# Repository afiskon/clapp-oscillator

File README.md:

# clapp-oscillator
Clapp oscillator schematic, PCB and simulations

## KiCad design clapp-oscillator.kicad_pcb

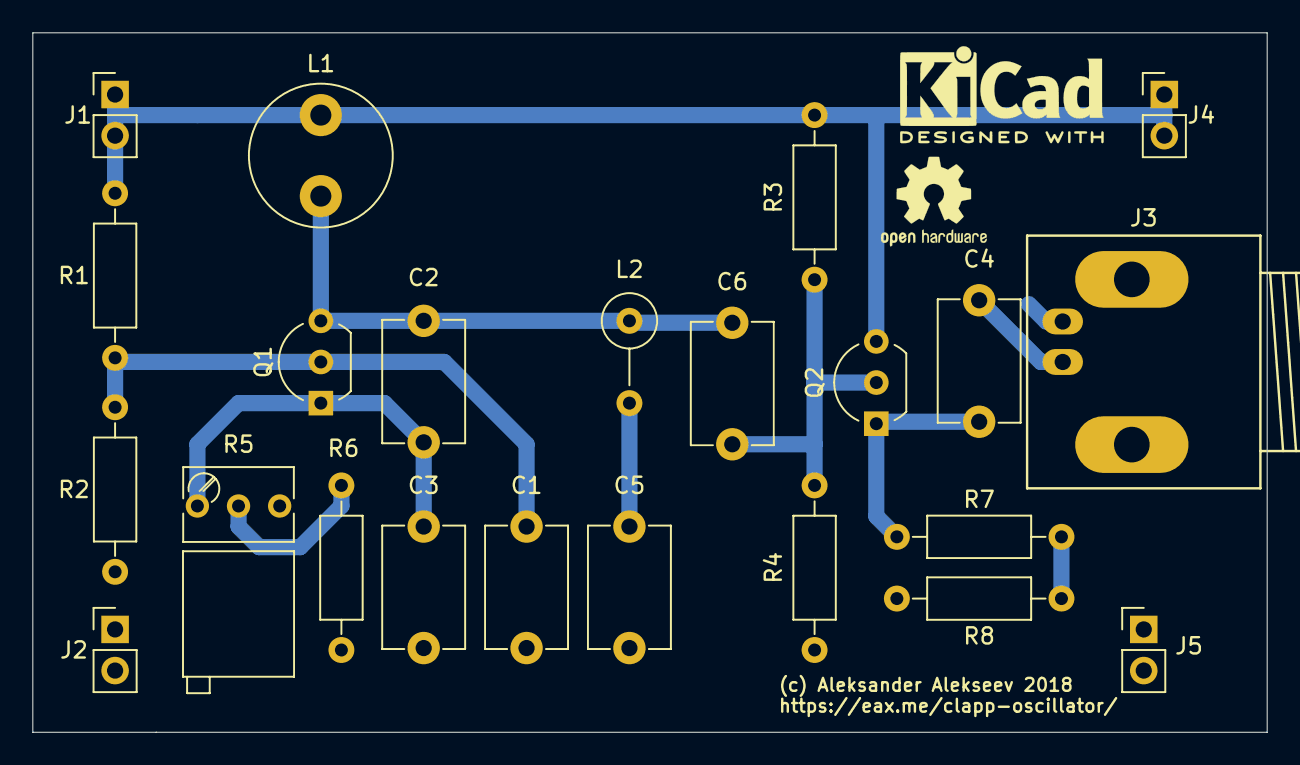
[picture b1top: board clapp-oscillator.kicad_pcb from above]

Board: 2 copper layers, 76.2 x 43.2 mm, 23 parts (0 on the bottom side), 11 nets.

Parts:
C1, C4, C6: 100nF; C_Disc_D7.5mm_W5.0mm_P7.50mm
C2, C5: 1nF; C_Disc_D7.5mm_W5.0mm_P7.50mm
C3: 10nF; C_Disc_D7.5mm_W5.0mm_P7.50mm
J1, J2, J4, J5: Conn_01x02; Pin_Header_Straight_1x02_Pitch2.54mm
J3: Conn_Coaxial; BNC_Socket_TYCO-AMP_LargePads
L1: 10mH; L_Radial_D8.7mm_P5.00mm_Fastron_07HCP
L2: 10uH; L_Axial_L7.0mm_D3.3mm_P5.08mm_Vertical_Fastron_MICC
Q1, Q2: 2N2222; TO-92_Inline_Wide
R1: 15K; R_Axial_DIN0207_L6.3mm_D2.5mm_P10.16mm_Horizontal
R2: 4.7K; R_Axial_DIN0207_L6.3mm_D2.5mm_P10.16mm_Horizontal
R3, R4: 1.5k; R_Axial_DIN0207_L6.3mm_D2.5mm_P10.16mm_Horizontal
R5: 1K; Potentiometer_Trimmer_Bourns_3266Y
R6: 1; R_Axial_DIN0207_L6.3mm_D2.5mm_P10.16mm_Horizontal
R7, R8: 12; R_Axial_DIN0207_L6.3mm_D2.5mm_P10.16mm_Horizontal

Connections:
+5V: J1.1, J1.2, J4.1, J4.2, L1.1, Q2.3, R1.1, R3.1
GND: C1.2, C3.2, C5.2, J2.1, J2.2, J3.2, J5.1, J5.2, R2.2, R4.2, R6.2, R8.2
unnamed: C1.1, Q1.2, R1.2, R2.1
unnamed: C2.1, C6.2, L1.2, L2.1, Q1.3
unnamed: C2.2, C3.1, Q1.1, R5.1
unnamed: C4.1, J3.1
unnamed: C4.2, Q2.1, R7.1
unnamed: C5.1, L2.2
unnamed: R5.2, R6.1
unnamed: R7.2, R8.1
SIG: C6.1, Q2.2, R3.2, R4.1

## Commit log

2018-09-11 Code moved from a sandbox repository
2018-09-11 Add frequencies.txt
2018-09-11 Specify L2 in frequencies.txt
2018-09-11 Add Qucs simulation
2018-09-11 Fix project description in README.md
